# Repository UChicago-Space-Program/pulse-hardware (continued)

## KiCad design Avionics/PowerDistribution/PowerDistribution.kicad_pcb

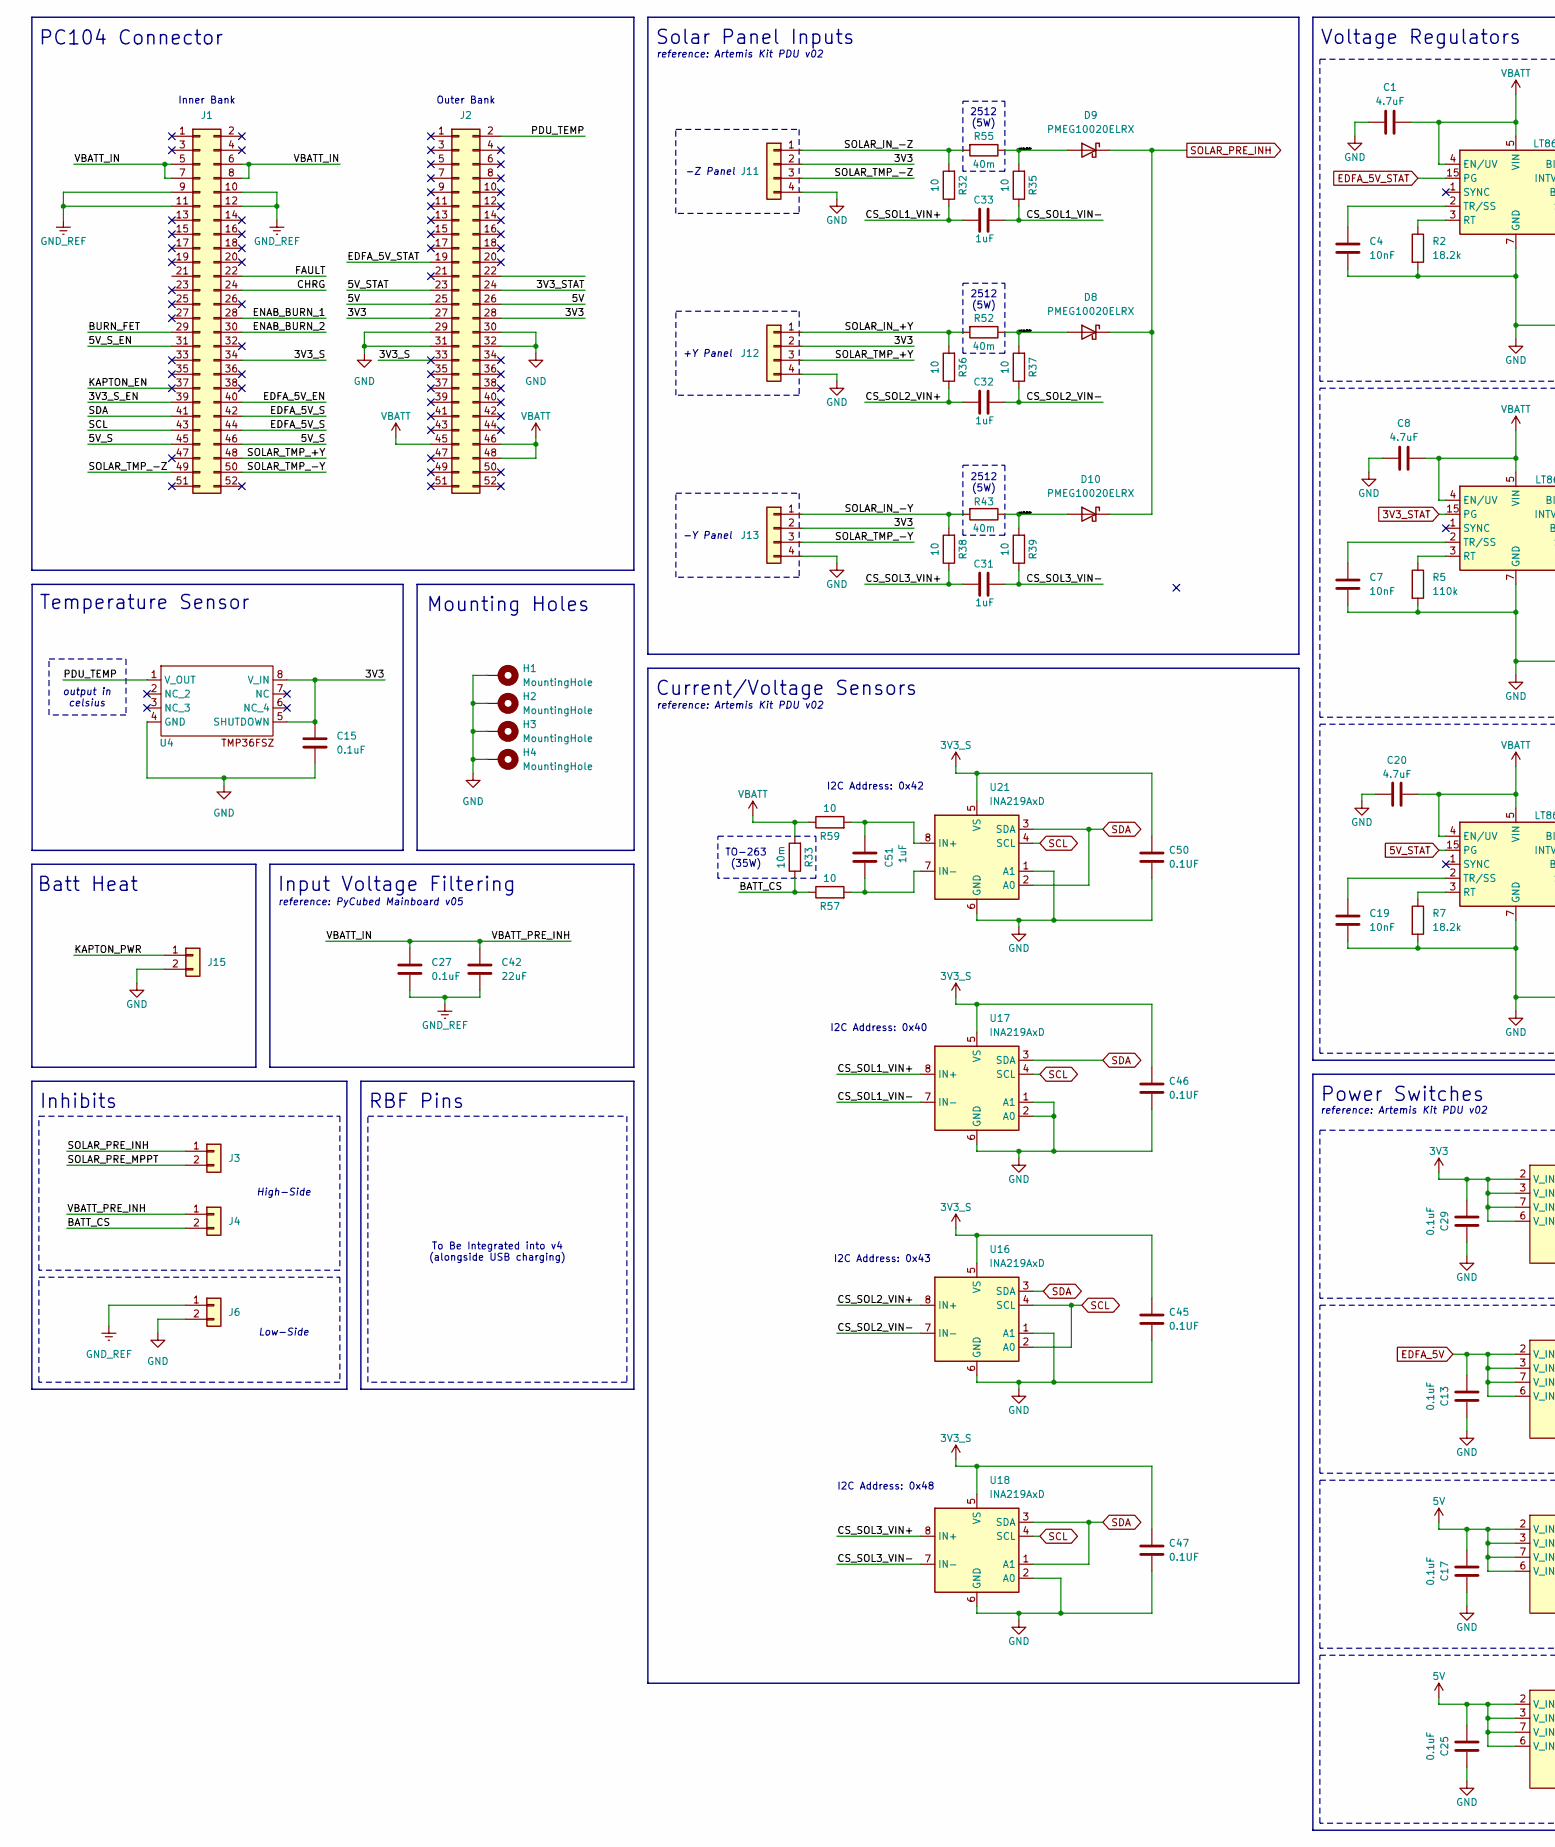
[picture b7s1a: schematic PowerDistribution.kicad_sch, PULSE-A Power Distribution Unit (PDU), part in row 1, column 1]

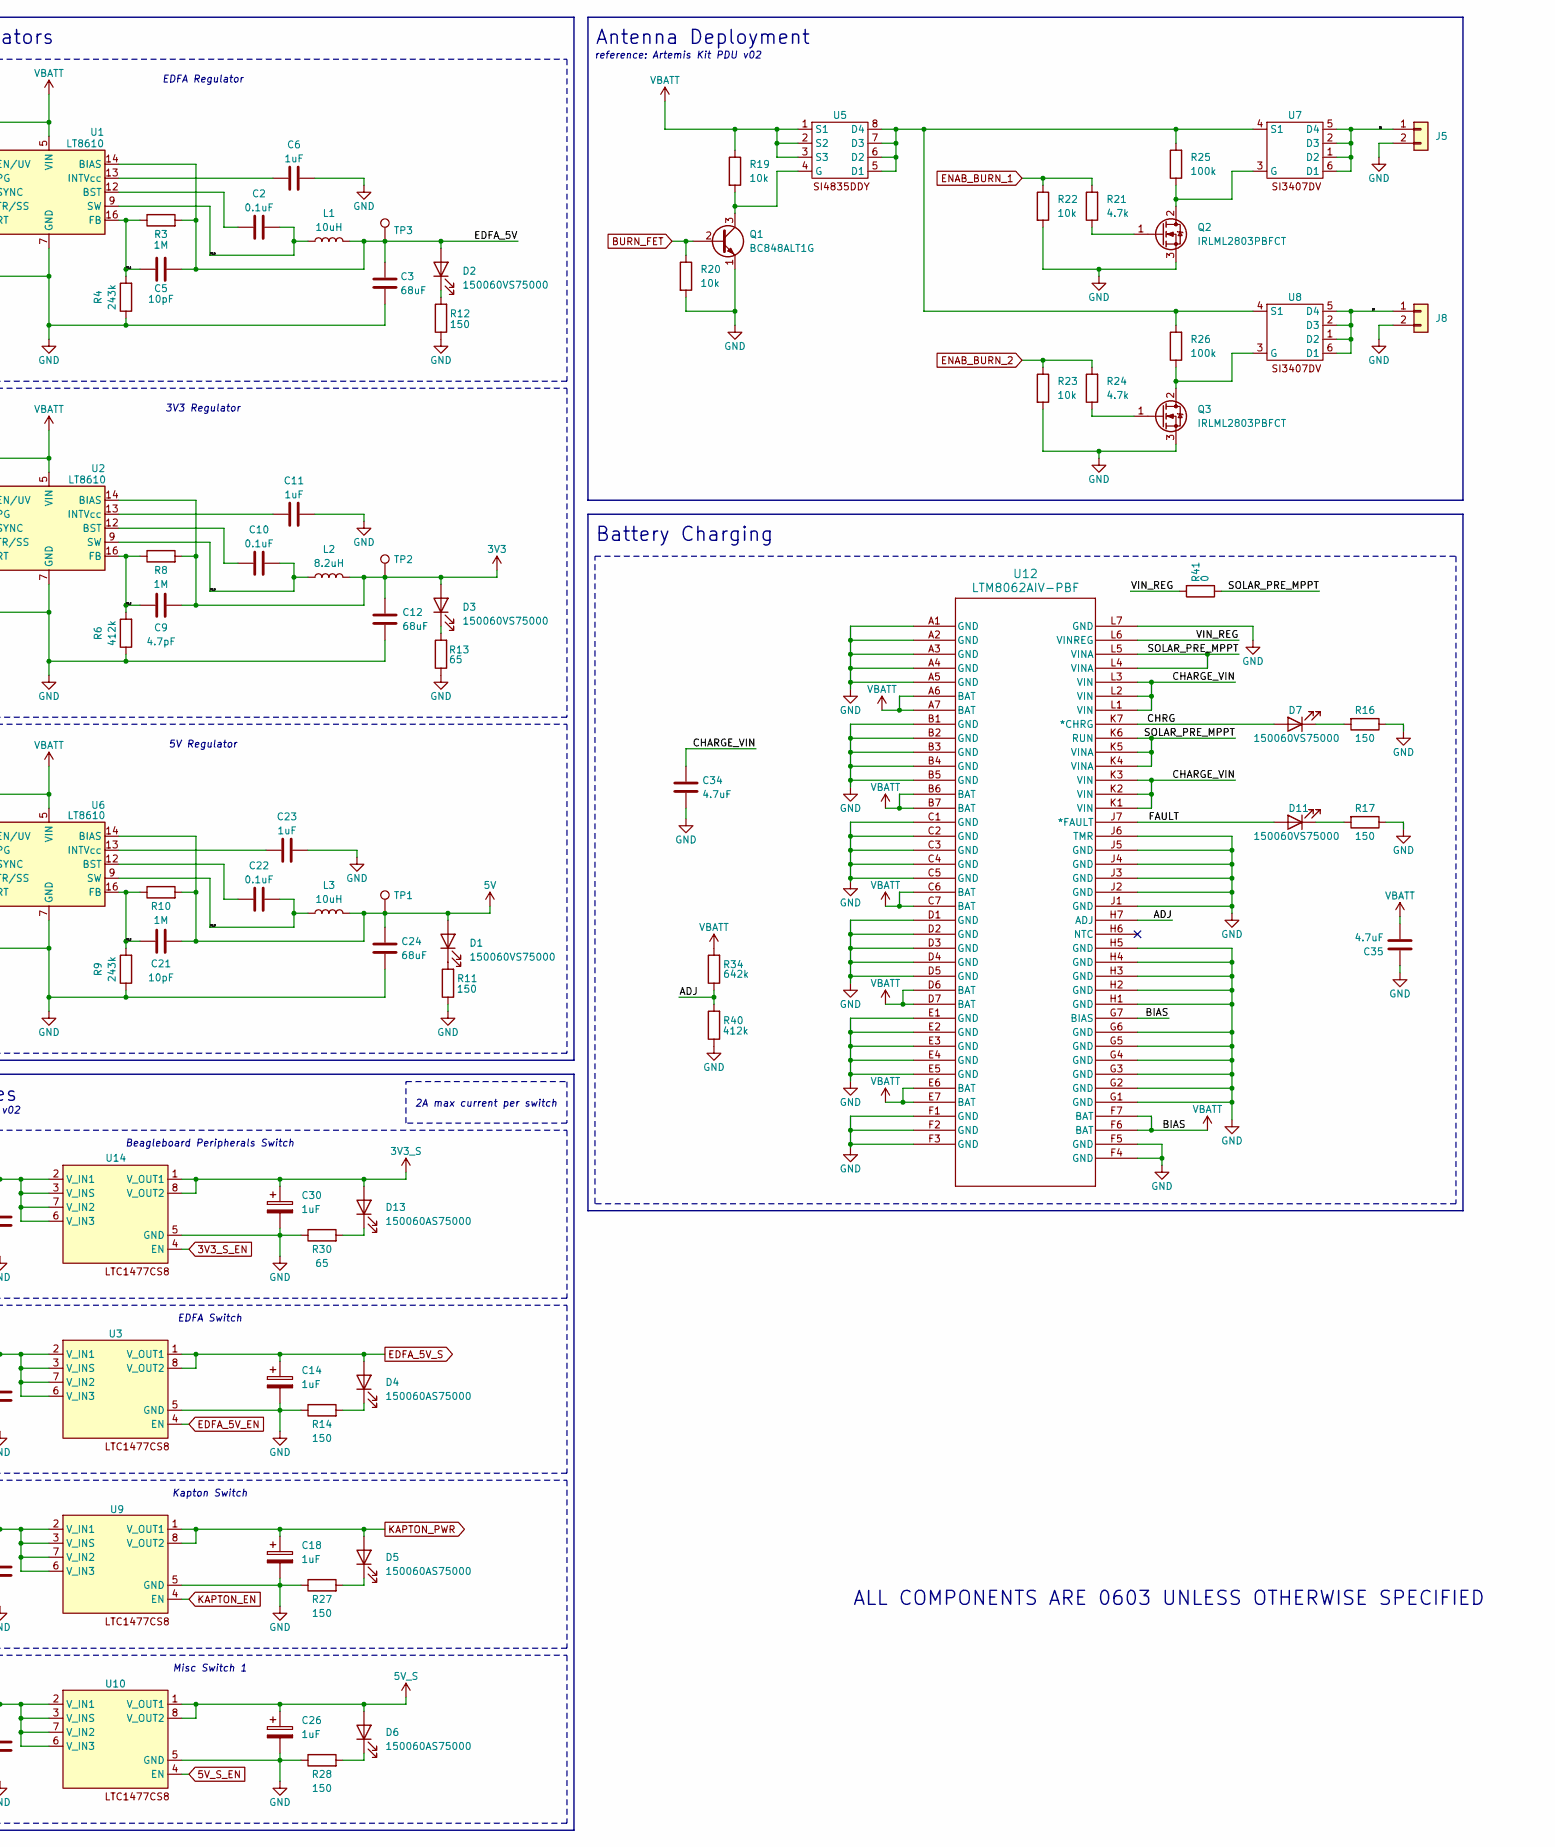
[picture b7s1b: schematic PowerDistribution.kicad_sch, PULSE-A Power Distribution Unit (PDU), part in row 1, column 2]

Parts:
C1, C8, C20: 4.7uF; C_0603_1608Metric
C2, C10, C22, C27: 0.1uF; C_0805_2012Metric
C3, C12, C24: 68uF; C_1206_3216Metric
C4, C7, C19: 10nF; C_0603_1608Metric
C5, C21: 10pF; C_0805_2012Metric
C6, C11, C14, C18, C23, C26, C30, C31, C32, C33, C51: 1uF; C_0603_1608Metric
C9: 4.7pF; C_0805_2012Metric
C13, C15, C17, C25, C29: 0.1uF; C_0603_1608Metric
C34: 4.7uF; C_1206_3216Metric
C35: 4.7uF; CP_EIA-3528-12_Kemet-T
C42: 22uF; C_0805_2012Metric
C45, C46, C47, C50: 0.1UF; C_0603_1608Metric
D1, D2, D3, D7, D11: 150060VS75000; LED_0603_1608Metric
D4, D5, D6, D13: 150060AS75000; LED_0603_1608Metric
D8, D9, D10: PMEG10020ELRX; Nexperia_CFP3_SOD-123W
H1, H2, H3, H4: MountingHole; MountingHole_3.2mm_M3_Pad_TopBottom
J1, J2: Conn_02x26_Odd_Even; PinHeader_2x26_P2.54mm_Vertical
J3, J4, J5, J6, J8, J15: Conn_01x02; Molex_Pico-Lock_205338-0002_1x02-1MP_P2.00mm_Horizontal
J11, J12, J13: Conn_01x04; Molex_Pico-Lock_205338-0004_1x04-1MP_P2.00mm_Horizontal
L1, L3: 10uH; L_Coilcraft_XxL4040
L2: 8.2uH; L_Coilcraft_XxL4040
Q1: BC848ALT1G; SOT-23-3
Q2, Q3: IRLML2803PBFCT; SOT-23-3
R2, R7: 18.2k; R_0603_1608Metric
R3, R8, R10: 1M; R_0805_2012Metric
R4, R9: 243k; R_0805_2012Metric
R5: 110k; R_0603_1608Metric
R6: 412k; R_0805_2012Metric
R11, R12, R14, R16, R17, R27, R28: 150; R_0603_1608Metric
R13, R30: 65; R_0603_1608Metric
R19, R20, R22, R23: 10k; R_0805_2012Metric
R21, R24: 4.7k; R_0805_2012Metric
R25, R26: 100k; R_0805_2012Metric
R32, R35, R36, R37, R38, R39, R57, R59: 10; R_0603_1608Metric
R33: 10m; R_2512_6332Metric
R34: 642k; R_0603_1608Metric
R40: 412k; R_0603_1608Metric
R41: 0; R_0603_1608Metric
R43, R52, R55: 40m; R_2512_6332Metric
TP1, TP2, TP3: TestPoint_Keystone_5000-5004_Miniature
U1, U2, U6: LT8610; MSOP-16-1EP_3x4.039mm_P0.5mm_EP1.651x2.845mm_ThermalVias
U3, U5, U9, U10, U14: SOIC-8_3.9x4.9mm_P1.27mm
U4: SOIC-8-1EP_3.9x4.9mm_P1.27mm_EP2.41x3.3mm
U7, U8: TSOP-6_1.65x3.05mm_P0.95mm
U12: LTM8062AIV-PBF; LGA-77
U16, U17, U18, U21: INA219AxD; SOIC-8_3.9x4.9mm_P1.27mm

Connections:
3V3: C9.2, C12.2, C15.2, C29.1, D3.2 (A), J2.27, J2.28, J11.2, J12.2, J13.2, L2.2, R8.2, TP2.1, U2.14 (BIAS), U4.5 (SHUTDOWN), U4.8 (V_IN), U14.2 (V_IN1), U14.3 (V_INS), U14.6 (V_IN3), U14.7 (V_IN2)
3V3_S: C30.1, C45.2, C46.2, C47.2, C50.2, D13.2 (A), J1.34, J2.33, U14.1 (V_OUT1), U14.8 (V_OUT2), U16.5 (VS), U17.5 (VS), U18.5 (VS), U21.5 (VS)
3V3_STAT: J2.24, U2.15 (PG)
3V3_S_EN: J1.39, U14.4 (EN)
5V: C17.1, C21.2, C24.2, C25.1, D1.2 (A), J2.25, J2.26, L3.2, R10.2, TP1.1, U6.14 (BIAS), U9.2 (V_IN1), U9.3 (V_INS), U9.6 (V_IN3), U9.7 (V_IN2), U10.2 (V_IN1), U10.3 (V_INS), U10.6 (V_IN3), U10.7 (V_IN2)
5V_S: C26.1, D6.2 (A), J1.45, J1.46, U10.1 (V_OUT1), U10.8 (V_OUT2)
5V_STAT: J2.23, U6.15 (PG)
5V_S_EN: J1.31, U10.4 (EN)
/ADJ: R34.1, R40.2, U12.H7 (ADJ)
/BATT_CS: J4.2, R33.1, R57.1
/CHARGE_VIN: C34.2, U12.K1 (VIN), U12.K2 (VIN), U12.K3 (VIN), U12.L1 (VIN), U12.L2 (VIN), U12.L3 (VIN)
/CHRG: D7.2 (A), J1.24, U12.K7 (*CHRG)
/CS_SOL1_VIN+: C33.2, R32.1, U17.8 (IN+)
/CS_SOL1_VIN-: C33.1, R35.1, U17.7 (IN-)
/CS_SOL2_VIN+: C32.2, R36.1, U16.8 (IN+)
/CS_SOL2_VIN-: C32.1, R37.1, U16.7 (IN-)
/CS_SOL3_VIN+: C31.2, R38.1, U18.8 (IN+)
/CS_SOL3_VIN-: C31.1, R39.1, U18.7 (IN-)
/FAULT: D11.2 (A), J1.22, U12.J7 (*FAULT)
/FB_1: C5.1, R3.1, R4.2, U1.16 (FB)
/FB_2: C9.1, R6.2, R8.1, U2.16 (FB)
/FB_3: C21.1, R9.2, R10.1, U6.16 (FB)
/PDU_TEMP: J2.2, U4.1 (V_OUT)
/SOLAR_IN_+Y: J12.1, R36.2, R52.2
/SOLAR_IN_-Y: J13.1, R38.2, R43.2
/SOLAR_IN_-Z: J11.1, R32.2, R55.2
/SOLAR_PRE_MPPT: J3.2, R41.1, U12.K4 (VINA), U12.K5 (VINA), U12.K6 (RUN), U12.L4 (VINA), U12.L5 (VINA)
/SOLAR_TMP_+Y: J1.48, J12.3
/SOLAR_TMP_-Y: J1.50, J13.3
/SOLAR_TMP_-Z: J1.49, J11.3
/SW_1: C2.2, L1.1, U1.9 (SW), U1.10 (SW), U1.11 (SW)
/SW_2: C10.2, L2.1, U2.9 (SW), U2.10 (SW), U2.11 (SW)
/SW_3: C22.2, L3.1, U6.9 (SW), U6.10 (SW), U6.11 (SW)
/VBATT_IN: C27.2, C42.2, J1.5, J1.6, J1.7, J1.8, J4.1
/VIN_REG: R41.2, U12.L6 (VINREG)
/b1: J5.1, U7.1 (D2), U7.2 (D3), U7.5 (D4), U7.6 (D1)
/b2: J8.1, U8.1 (D2), U8.2 (D3), U8.5 (D4), U8.6 (D1)
/sol_1_diode: D9.2 (A), R35.2, R55.1
/sol_2_diode: D8.2 (A), R37.2, R52.1
/sol_3_diode: D10.2 (A), R39.2, R43.1
BURN_FET: J1.29, Q1.2 (B), R20.1
EDFA_5V: C3.2, C5.2, C13.1, D2.2 (A), L1.2, R3.2, TP3.1, U1.14 (BIAS), U3.2 (V_IN1), U3.3 (V_INS), U3.6 (V_IN3), U3.7 (V_IN2)
EDFA_5V_EN: J1.40, U3.4 (EN)
EDFA_5V_S: C14.1, D4.2 (A), J1.42, J1.44, U3.1 (V_OUT1), U3.8 (V_OUT2)
EDFA_5V_STAT: J2.19, U1.15 (PG)
ENAB_BURN_1: J1.28, R21.2, R22.1
ENAB_BURN_2: J1.30, R23.1, R24.2
GND: C1.1, C3.1, C4.1, C6.2, C7.1, C8.1, C11.2, C12.1, C13.2, C14.2, C15.1, C17.2, C18.2, C19.1, C20.2, C23.2, C24.1, C25.2, C26.2, C29.2, C30.2, C34.1, C35.2, C45.1, C46.1, C47.1, C50.1, H1.MP, H2.MP, H3.MP, H4.MP, J2.29, J2.30, J2.31, J2.32, J5.2, J6.2, J8.2, J11.4, J12.4, J13.4, J15.2, Q1.1 (E), Q2.3 (S), Q3.3 (S), R2.2, R4.1, R5.2, R6.1, R7.2, R9.1, R11.1, R12.1, R13.1, R14.1, R16.1, R17.1, R20.2, R22.2, R23.2, R27.1, R28.1, R30.1, R40.1, U1.7 (GND), U1.8 (GND), U1.17 (GND), U2.7 (GND), U2.8 (GND), U2.17 (GND), U3.5 (GND), U4.4 (GND), U6.7 (GND), U6.8 (GND), U6.17 (GND), U9.5 (GND), U10.5 (GND), U12.A1 (GND), U12.A2 (GND), U12.A3 (GND), U12.A4 (GND), U12.A5 (GND), U12.B1 (GND), U12.B2 (GND), U12.B3 (GND), U12.B4 (GND), U12.B5 (GND), U12.C1 (GND), U12.C2 (GND), U12.C3 (GND), U12.C4 (GND), U12.C5 (GND), U12.D1 (GND), U12.D2 (GND), U12.D3 (GND), U12.D4 (GND), U12.D5 (GND), U12.E1 (GND), U12.E2 (GND), U12.E3 (GND), U12.E4 (GND), U12.E5 (GND), U12.F1 (GND), U12.F2 (GND), U12.F3 (GND), U12.F4 (GND), U12.F5 (GND), U12.G1 (GND), U12.G2 (GND), U12.G3 (GND), U12.G4 (GND), U12.G5 (GND), U12.G6 (GND), U12.H1 (GND), U12.H2 (GND), U12.H3 (GND), U12.H4 (GND), U12.H5 (GND), U12.J1 (GND), U12.J2 (GND), U12.J3 (GND), U12.J4 (GND), U12.J5 (GND), U12.J6 (TMR), U12.L7 (GND), U14.5 (GND), U16.1 (A1), U16.6 (GND), U17.1 (A1), U17.2 (A0), U17.6 (GND), U18.2 (A0), U18.6 (GND), U21.1 (A1), U21.6 (GND)
GND_REF: C27.1, C42.1, J1.9, J1.10, J1.11, J1.12, J6.1
KAPTON_EN: J1.37, U9.4 (EN)
KAPTON_PWR: C18.1, D5.2 (A), J15.1, U9.1 (V_OUT1), U9.8 (V_OUT2)
unnamed: D1.1 (K), R11.2
unnamed: D2.1 (K), R12.2
unnamed: D3.1 (K), R13.2
unnamed: D4.1 (K), R14.2
unnamed: D5.1 (K), R27.2
unnamed: D6.1 (K), R28.2
unnamed: D7.1 (K), R16.2
unnamed: D11.1 (K), R17.2
unnamed: D13.1 (K), R30.2
unnamed: Q1.3 (C), R19.2, U5.4 (G)
unnamed: Q2.2 (D), R25.1, U7.3 (G)
unnamed: Q2.1 (G), R21.1
unnamed: Q3.2 (D), R26.1, U8.3 (G)
unnamed: Q3.1 (G), R24.1
unnamed: C2.1, U1.12 (BST)
unnamed: C6.1, U1.13 (INTVcc)
unnamed: R2.1, U1.3 (RT)
unnamed: C4.2, U1.2 (TR/SS)
unnamed: C10.1, U2.12 (BST)
unnamed: C11.1, U2.13 (INTVcc)
unnamed: R5.1, U2.3 (RT)
unnamed: C7.2, U2.2 (TR/SS)
unnamed: R25.2, R26.2, U5.5 (D1), U5.6 (D2), U5.7 (D3), U5.8 (D4), U7.4 (S1), U8.4 (S1)
unnamed: C22.1, U6.12 (BST)
unnamed: C23.1, U6.13 (INTVcc)
unnamed: R7.1, U6.3 (RT)
unnamed: C19.2, U6.2 (TR/SS)
unnamed: C51.1, R59.2, U21.8 (IN+)
unnamed: C51.2, R57.2, U21.7 (IN-)
SCL: J1.43, U16.2 (A0), U16.4 (SCL), U17.4 (SCL), U18.4 (SCL), U21.4 (SCL)
SDA: J1.41, U16.3 (SDA), U17.3 (SDA), U18.1 (A1), U18.3 (SDA), U21.2 (A0), U21.3 (SDA)
SOLAR_PRE_INH: D8.1 (K), D9.1 (K), D10.1 (K), J3.1
VBATT: C1.2, C8.2, C20.1, C35.1, J2.45, J2.46, J2.48, R19.1, R33.2, R34.2, R59.1, U1.4 (EN/UV), U1.5 (VIN), U1.6 (VIN), U2.4 (EN/UV), U2.5 (VIN), U2.6 (VIN), U5.1 (S1), U5.2 (S2), U5.3 (S3), U6.4 (EN/UV), U6.5 (VIN), U6.6 (VIN), U12.A6 (BAT), U12.A7 (BAT), U12.B6 (BAT), U12.B7 (BAT), U12.C6 (BAT), U12.C7 (BAT), U12.D6 (BAT), U12.D7 (BAT), U12.E6 (BAT), U12.E7 (BAT), U12.F6 (BAT), U12.F7 (BAT), U12.G7 (BIAS)

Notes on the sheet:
5V Regulator
Power Switches
PC104 Connector
Voltage Regulators
reference: Artemis Kit PDU v02
2512 (5W)
Temperature Sensor
Current/Voltage Sensors
Kapton Switch
3V3 Regulator
Antenna Deployment
I2C Address: 0x48
I2C Address: 0x43
Batt Heat
Low-Side
Beagleboard Peripherals Switch
ALL COMPONENTS ARE 0603 UNLESS OTHERWISE SPECIFIED
Outer Bank
I2C Address: 0x42
RBF Pins
Battery Charging
High-Side
Inner Bank
Solar Panel Inputs
-Z Panel
To Be Integrated into v4 (alongside USB charging)
reference: PyCubed Mainboard v05
I2C Address: 0x40
EDFA Switch
Misc Switch 1
output in celsius
2A max current per switch
+Y Panel
Mounting Holes
Inhibits
Input Voltage Filtering
-Y Panel
EDFA Regulator
TO-263 (35W)

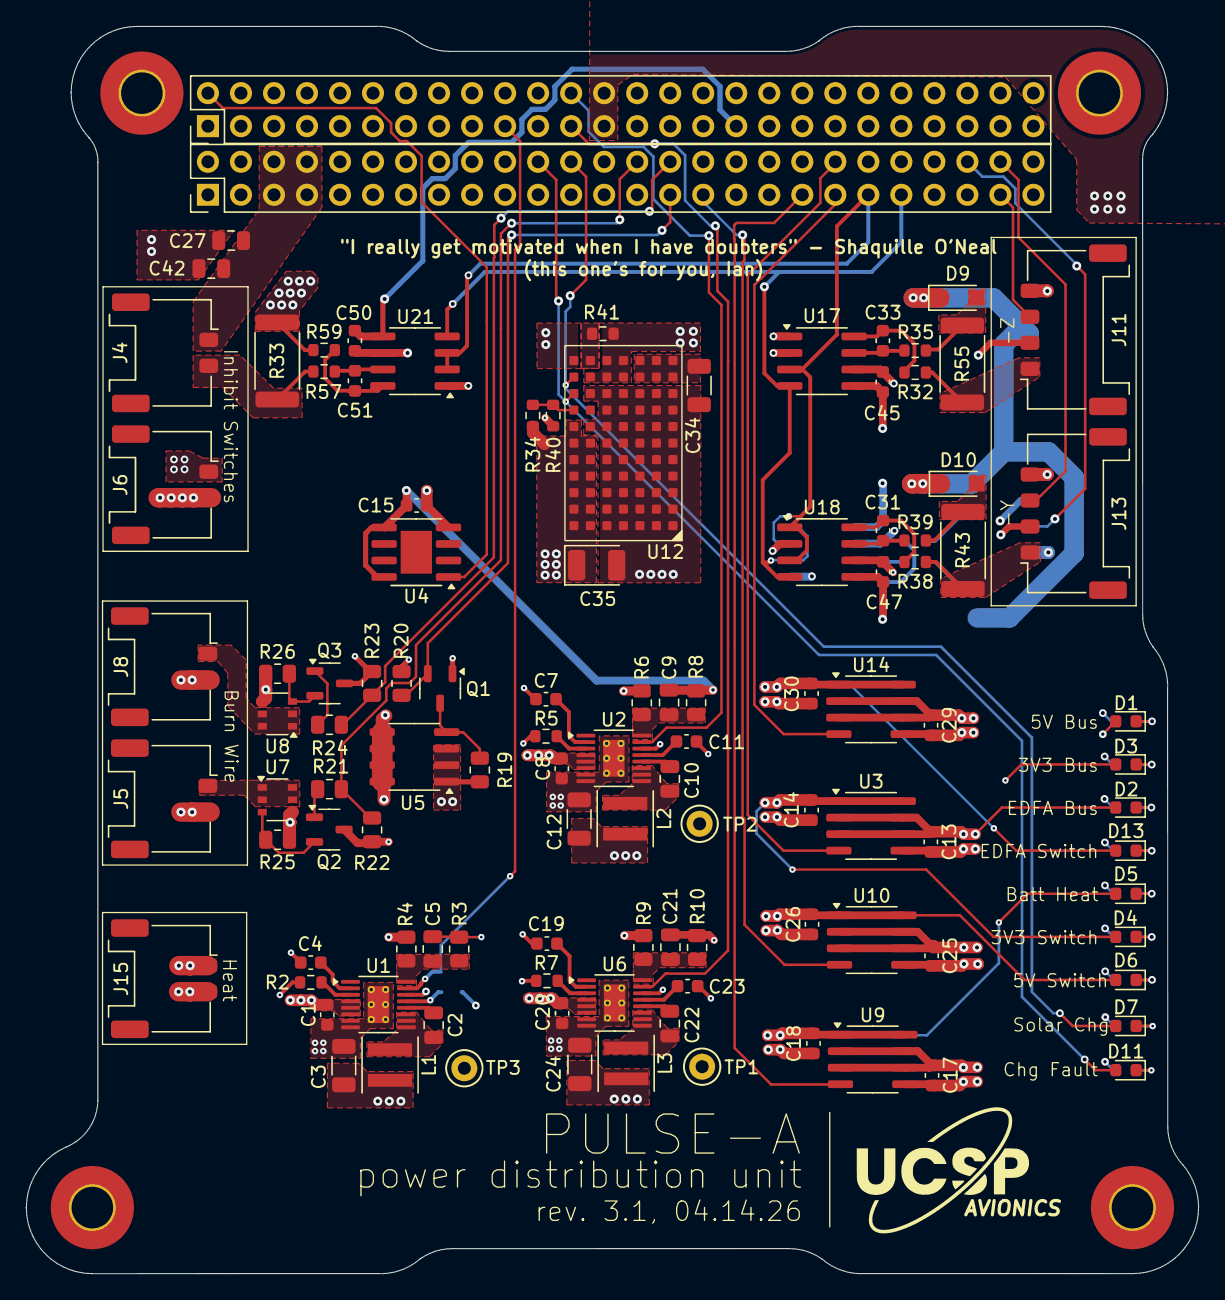
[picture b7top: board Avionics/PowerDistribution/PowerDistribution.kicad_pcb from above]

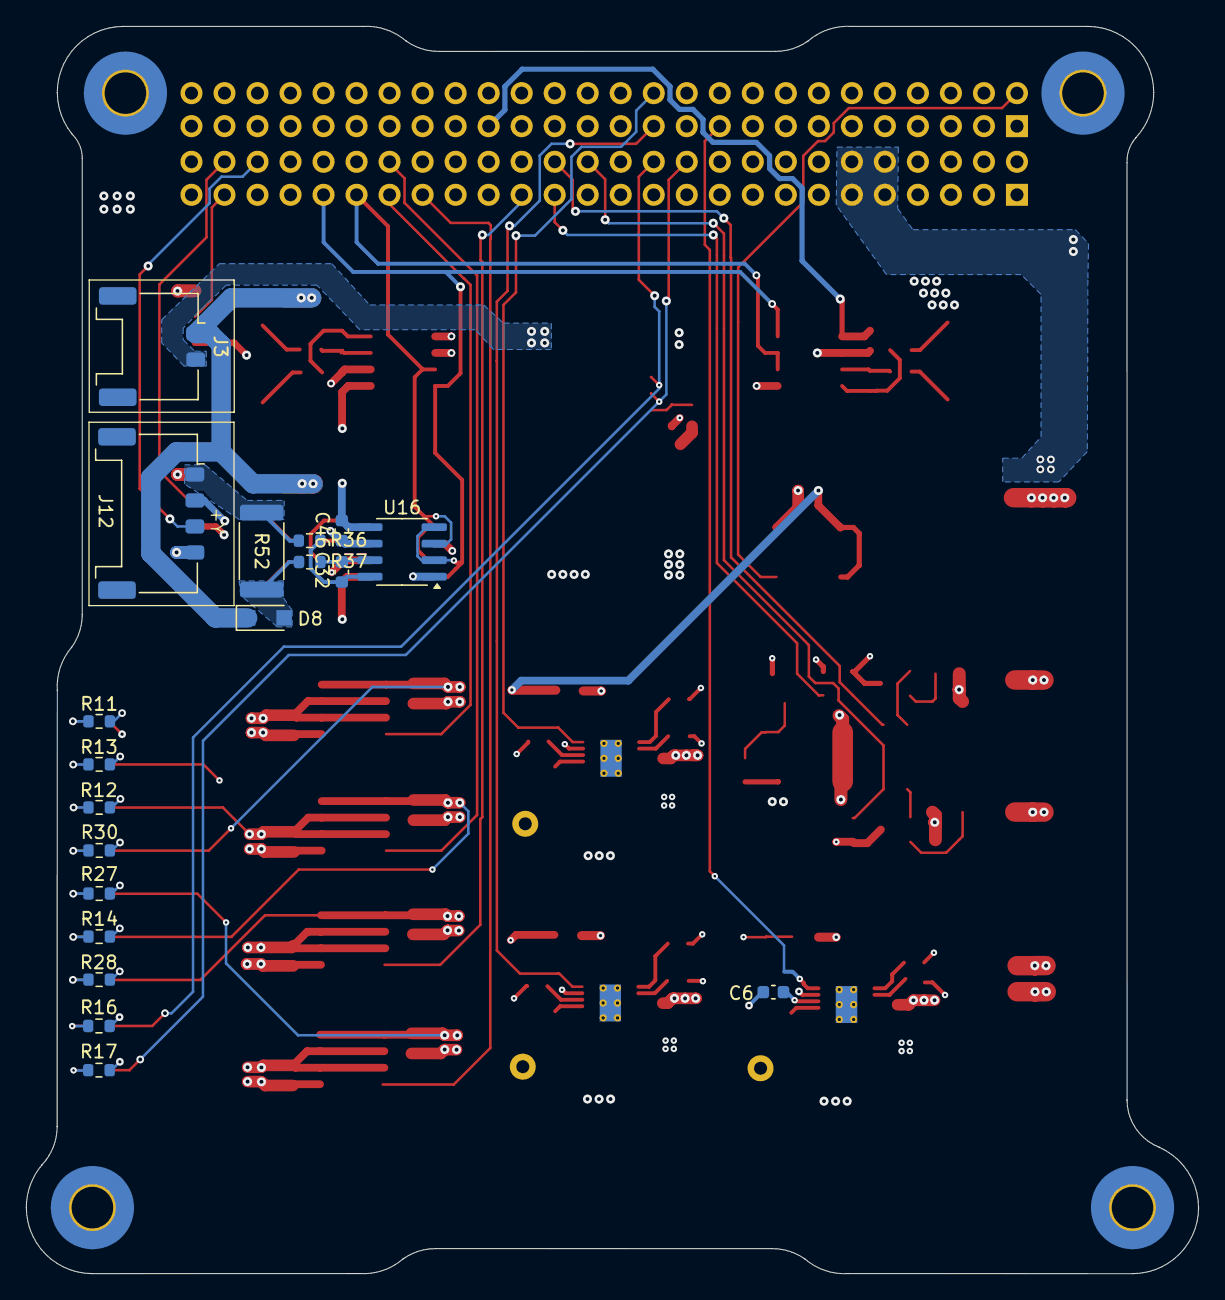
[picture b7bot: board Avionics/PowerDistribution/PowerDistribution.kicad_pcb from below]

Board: 4 copper layers, 90.2 x 96.0 mm, 132 parts (19 on the bottom side), 84 nets.

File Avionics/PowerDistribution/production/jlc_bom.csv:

Designator,Footprint,Quantity,Value,LCSC Part #
"C1, C20, C8",0603,3,4.7uF,
"C10, C2, C22, C27",0805,4,0.1uF,
"C11, C14, C18, C23, C26, C30, C31, C32, C33, C51, C6",0603,11,1uF,
"C12, C24, C3",1206,3,68uF,
"C13, C15, C17, C25, C29, C45, C46, C47, C50",0603,9,0.1uF,
"C19, C4, C7",0603,3,10nF,
"C21, C5",0805,2,10pF,
C34,1206,1,4.7uF,
C35,CP_EIA-3528-12_Kemet-T,1,4.7uF,
C42,0805,1,22uF,
C9,0805,1,4.7pF,
"D1, D11, D2, D3, D7",0603,5,150060VS75000,
"D10, D8, D9",Nexperia_CFP3_SOD-123W,3,PMEG10020ELRX,
"D13, D4, D5, D6",0603,4,150060AS75000,
"J1, J2",PinHeader_2x26_P2.54mm_Vertical,2,Conn_02x26_Odd_Even,
"J11, J12, J13",Molex_Pico-Lock_205338-0004_1x04-1MP_P2.00mm_Horizontal,3,Conn_01x04,
"J15, J3, J4, J5, J6, J8",Molex_Pico-Lock_205338-0002_1x02-1MP_P2.00mm_Horizontal,6,Conn_01x02,
L1,L_Coilcraft_XxL4040,1,10uH,
L2,L_Coilcraft_XxL4040,1,8.2uH,
L3,L_Coilcraft_XxL4040,1,4.7uH,
Q1,SOT-23-3,1,BC848ALT1G,
"Q2, Q3",SOT-23-3,2,IRLML2803PBFCT,
"R10, R3, R8",0805,3,1M,
"R11, R12, R14, R16, R17, R27, R28",0603,7,150,
"R13, R30",0603,2,65,
"R19, R20, R22, R23",0805,4,10k,
"R2, R7",0603,2,18.2k,
"R21, R24",0805,2,4.7k,
"R25, R26",0805,2,100k,
"R32, R35, R36, R37, R38, R39, R57, R59",0603,8,10,
R33,2512,1,10m,
R34,0603,1,642k,
"R4, R9",0805,2,243k,
R40,0603,1,412k,
R41,0603,1,0,
"R43, R52, R55",2512,3,40m,
R5,0603,1,110k,
R6,0805,1,412k,
"TP1, TP2, TP3",TestPoint_Keystone_5000-5004_Miniature,3,~,
"U1, U2, U6",MSOP-16-1EP_3x4.039mm_P0.5mm_EP1.651x2.845mm_ThermalVias,3,LT8610,
"U10, U14, U3, U5, U9",SOIC-8_3.9x4.9mm_P1.27mm,5,~,
U12,LGA-77,1,LTM8062AIV-PBF,
"U16, U17, U18, U21",SOIC-8_3.9x4.9mm_P1.27mm,4,INA219AxD,
U4,SOIC-8-1EP_3.9x4.9mm_P1.27mm_EP2.41x3.3mm,1,~,
"U7, U8",TSOP-6_1.65x3.05mm_P0.95mm,2,~,

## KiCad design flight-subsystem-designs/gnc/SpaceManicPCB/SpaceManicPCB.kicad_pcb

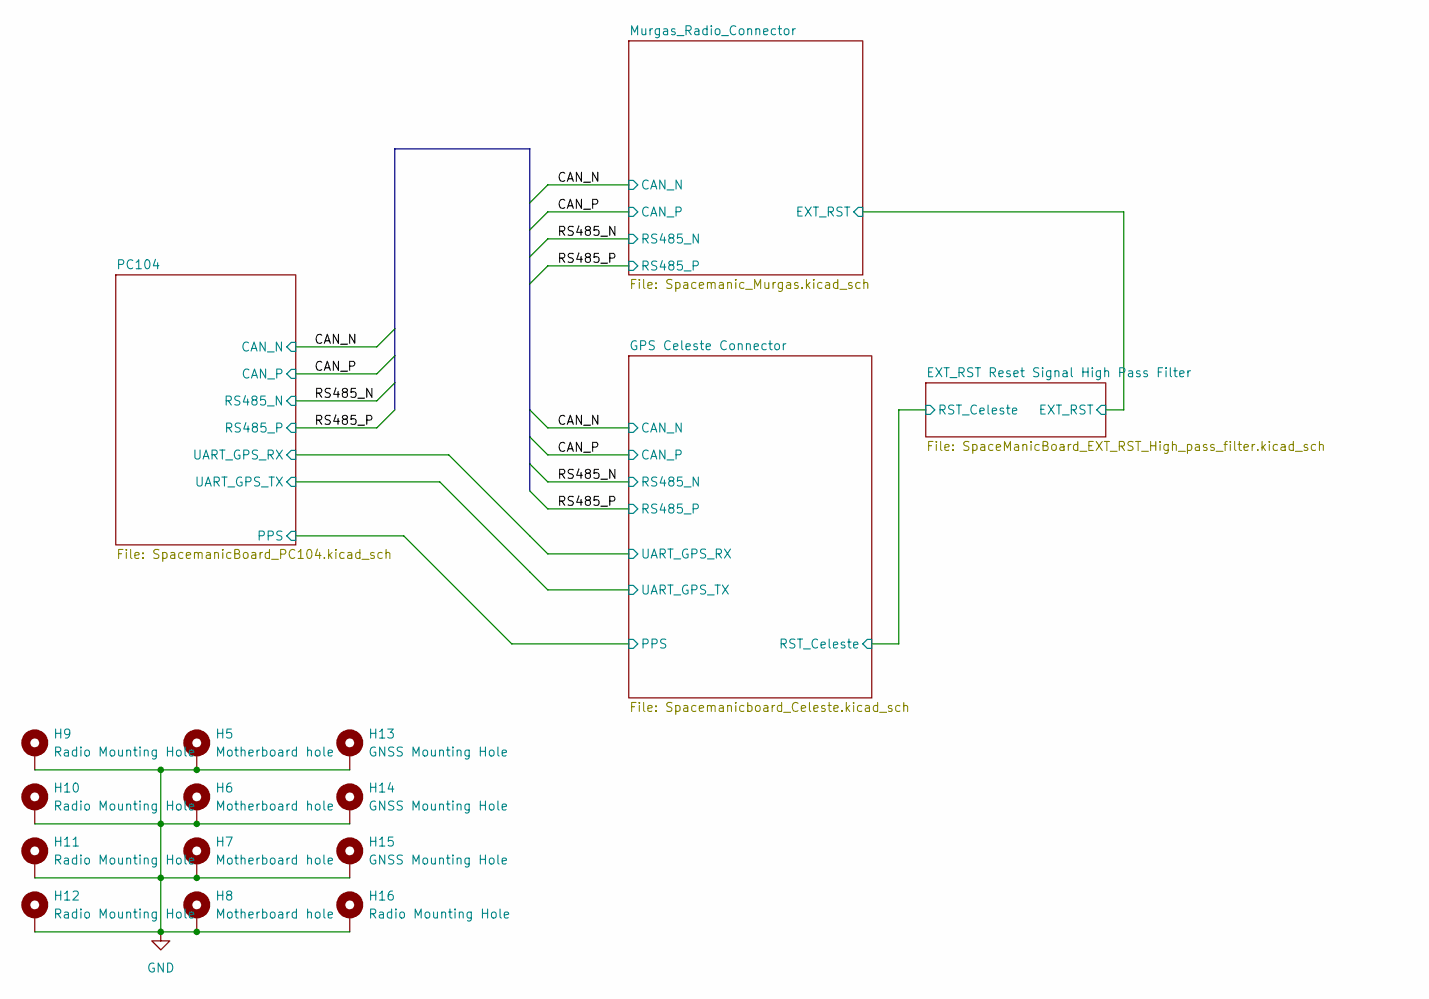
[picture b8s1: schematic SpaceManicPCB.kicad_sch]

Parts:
H5, H6, H7, H8: Motherboard hole; MountingHole_3.2mm_M3_DIN965_Pad_TopBottom
H9, H10, H11, H12, H16: Radio Mounting Hole; MountingHole_2.5mm
H13, H14, H15: GNSS Mounting Hole; MountingHole_2.5mm

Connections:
GND: H5.1, H6.1, H7.1, H8.1, H9.1, H10.1, H11.1, H12.1, H13.1, H14.1, H15.1, H16.1; also elsewhere on the board

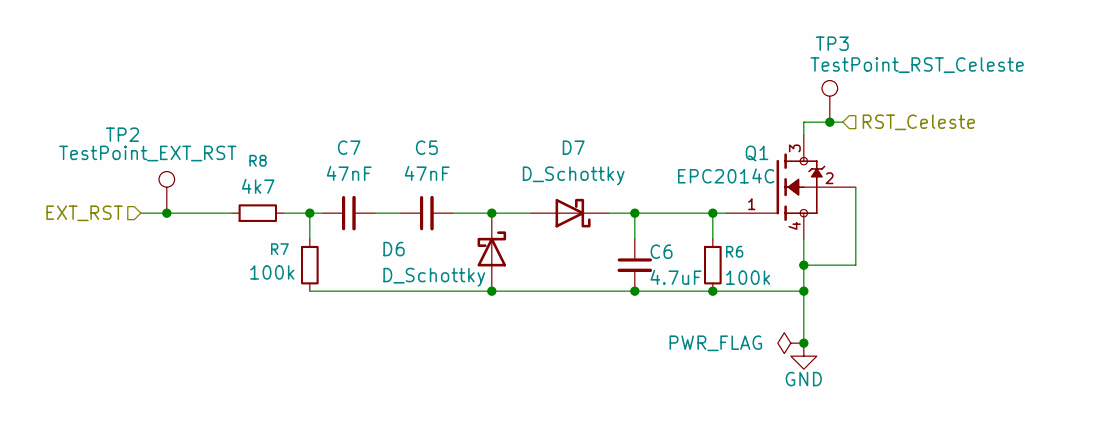
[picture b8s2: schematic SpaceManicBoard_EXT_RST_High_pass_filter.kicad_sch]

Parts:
C5, C7: 47nF; C_0603_1608Metric
C6: 4.7uF; C_0603_1608Metric
D6, D7: D_Schottky; D_0402_1005Metric
Q1: EPC2014C; TRANS_EPC2014C; PARTREV N/A
R6, R7: 100k; R_0603_1608Metric
R8: 4k7; R_0402_1005Metric
TP2: TestPoint_EXT_RST; TestPoint_Pad_D1.5mm
TP3: TestPoint_RST_Celeste; TestPoint_Pad_D1.5mm

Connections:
/EXT_RST Reset Signal High Pass Filter/EXT_RST: R8.1, TP2.1; also elsewhere on the board
/EXT_RST Reset Signal High Pass Filter/RST_Celeste: Q1.3, Q1.5, TP3.1; also elsewhere on the board
GND: C6.2, D6.2 (A), Q1.2, Q1.4, R6.2, R7.2; also elsewhere on the board
unnamed: C5.1, C7.2
unnamed: C7.1, R7.1, R8.2
unnamed: C5.2, D6.1 (K), D7.2 (A)
unnamed: C6.1, D7.1 (K), Q1.1, R6.1

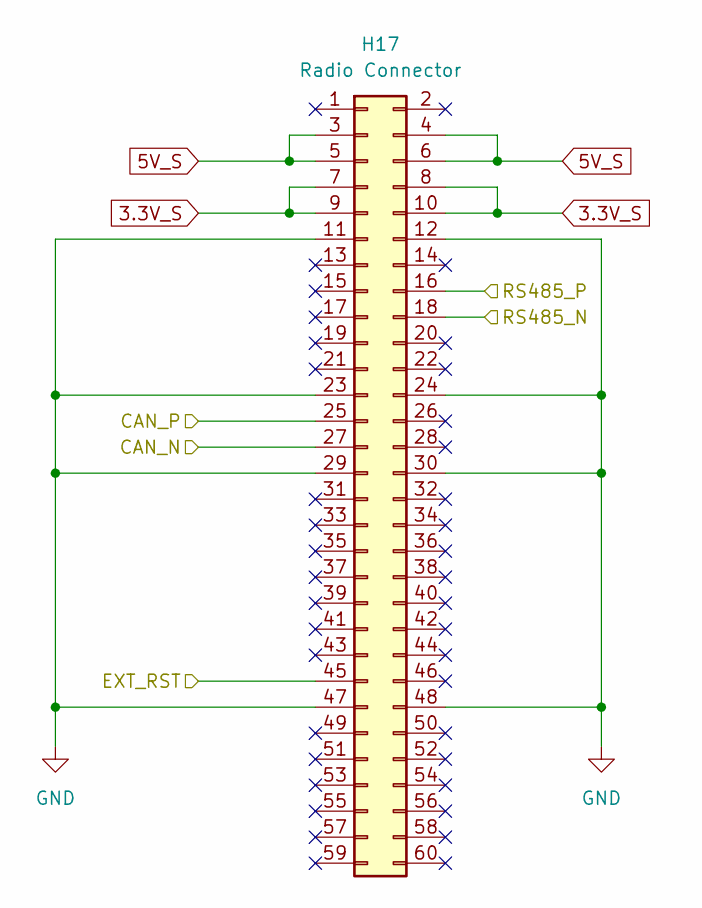
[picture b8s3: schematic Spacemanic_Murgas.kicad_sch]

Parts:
H17: Radio Connector; CON_MolexSlimStack_54363-0689

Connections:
3.3V_S: H17.7, H17.8, H17.9, H17.10; also elsewhere on the board
5V_S: H17.3, H17.4, H17.5, H17.6; also elsewhere on the board
/CAN_N: H17.27; also elsewhere on the board
/CAN_P: H17.25; also elsewhere on the board
/EXT_RST Reset Signal High Pass Filter/EXT_RST: H17.45; also elsewhere on the board
/RS485_N: H17.18; also elsewhere on the board
/RS485_P: H17.16; also elsewhere on the board
GND: H17.11, H17.12, H17.23, H17.24, H17.29, H17.30, H17.47, H17.48; also elsewhere on the board

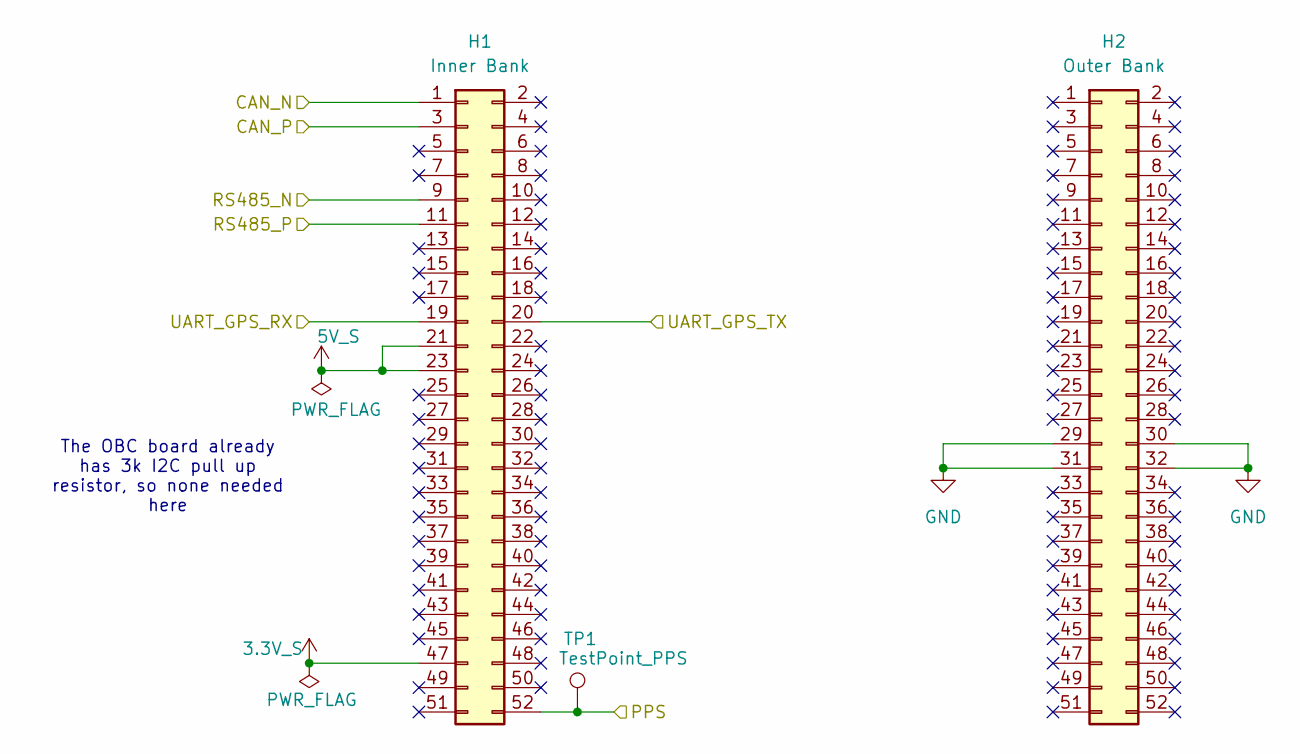
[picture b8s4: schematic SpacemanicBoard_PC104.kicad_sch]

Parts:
H1: Inner Bank; PinHeader_2x26_P2.54mm_Vertical
H2: Outer Bank; PinHeader_2x26_P2.54mm_Vertical
TP1: TestPoint_PPS; TestPoint_Pad_D1.5mm

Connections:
3.3V_S: H1.47; also elsewhere on the board
5V_S: H1.21, H1.23; also elsewhere on the board
/CAN_N: H1.1; also elsewhere on the board
/CAN_P: H1.3; also elsewhere on the board
/GPS Celeste Connector/PPS: H1.52, TP1.1; also elsewhere on the board
/GPS Celeste Connector/UART_GPS_RX: H1.19; also elsewhere on the board
/GPS Celeste Connector/UART_GPS_TX: H1.20; also elsewhere on the board
/RS485_N: H1.9; also elsewhere on the board
/RS485_P: H1.11; also elsewhere on the board
GND: H2.29, H2.30, H2.31, H2.32; also elsewhere on the board

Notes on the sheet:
The OBC board already has 3k I2C pull up resistor, so none needed here

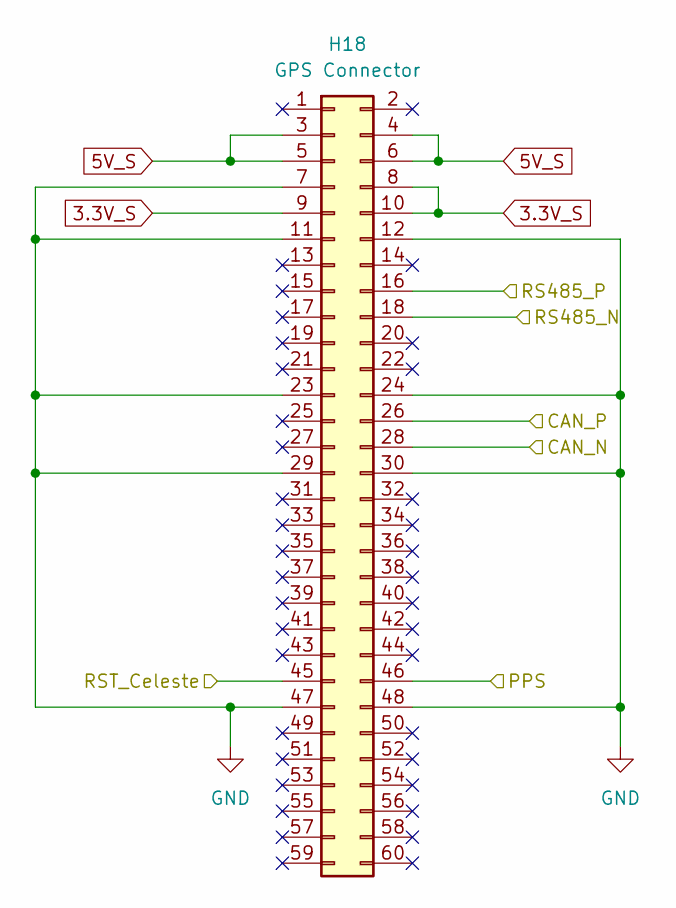
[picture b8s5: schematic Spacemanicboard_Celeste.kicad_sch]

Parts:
H18: GPS Connector; CON_MolexSlimStack_54363-0689

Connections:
3.3V_S: H18.8, H18.9, H18.10; also elsewhere on the board
5V_S: H18.3, H18.4, H18.5, H18.6; also elsewhere on the board
/CAN_N: H18.28; also elsewhere on the board
/CAN_P: H18.26; also elsewhere on the board
/EXT_RST Reset Signal High Pass Filter/RST_Celeste: H18.45; also elsewhere on the board
/GPS Celeste Connector/PPS: H18.46; also elsewhere on the board
/GPS Celeste Connector/UART_GPS_RX: H18.37; also elsewhere on the board
/GPS Celeste Connector/UART_GPS_TX: H18.35; also elsewhere on the board
/RS485_N: H18.18; also elsewhere on the board
/RS485_P: H18.16; also elsewhere on the board
GND: H18.7, H18.11, H18.12, H18.23, H18.24, H18.29, H18.30, H18.47, H18.48; also elsewhere on the board
